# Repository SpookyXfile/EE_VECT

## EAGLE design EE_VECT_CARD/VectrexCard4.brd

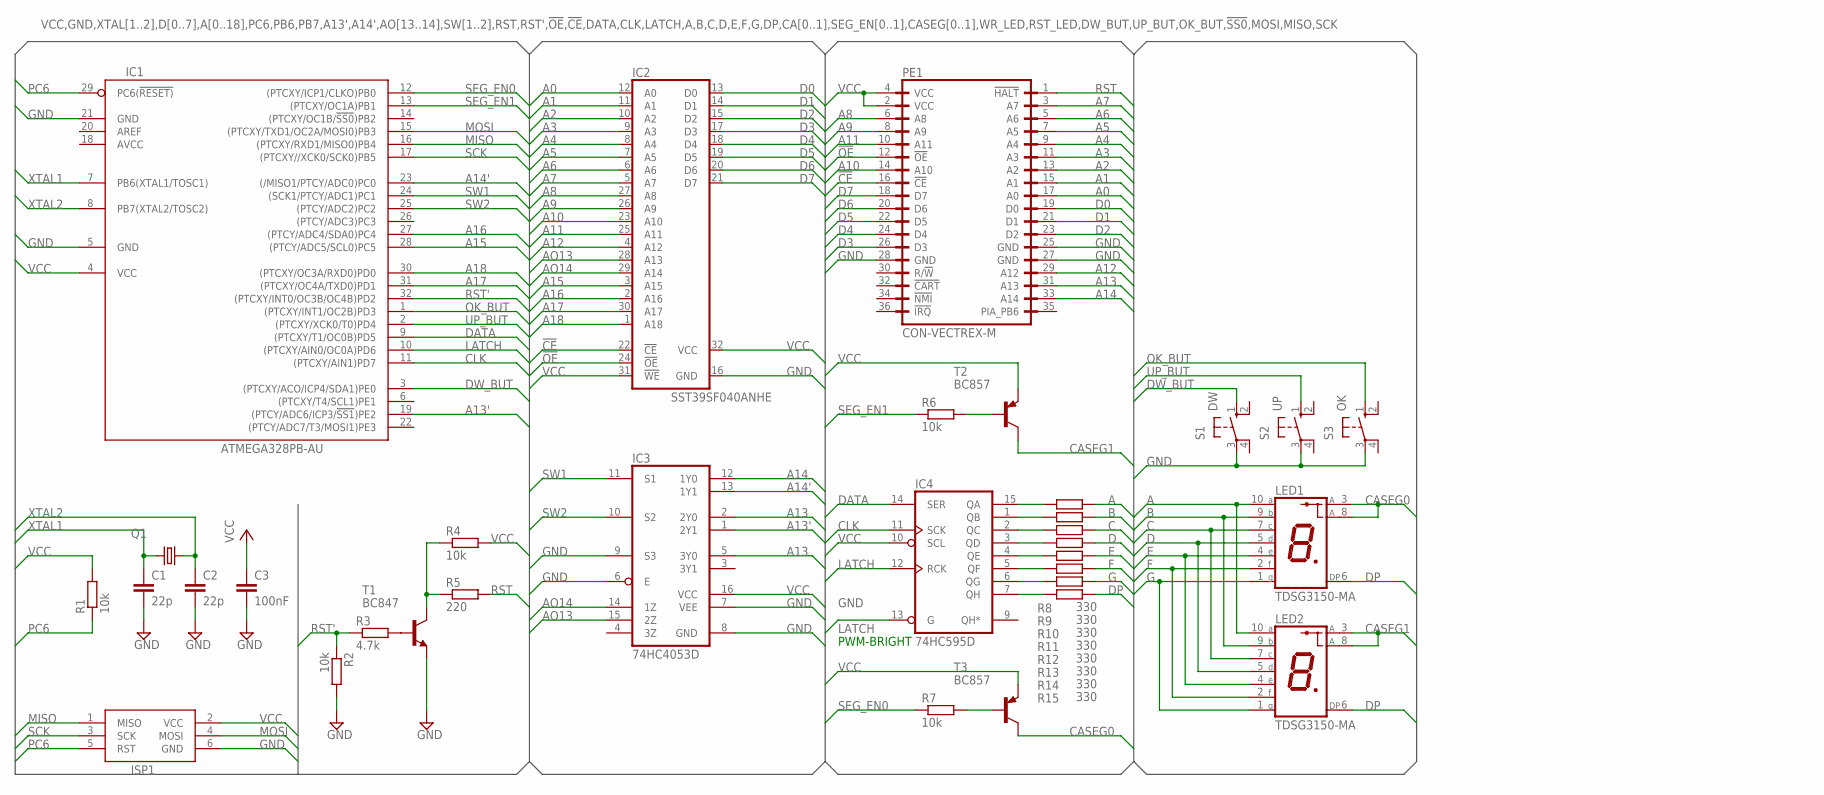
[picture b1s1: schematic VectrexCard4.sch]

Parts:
C1, C2: 22p; C2012
C3: 100nF; C050-025X075
IC1: ATMEGA328PB-AU; TQFP32-08
IC2: SST39SF040ANHE; S32
IC3: 74HC4053D; SO16
IC4: 74HC595D; SO16
ISP1: AVRISP-6; AVRISP
LED1, LED2: TDSG3150-MA; LA-401
PE1: CON-VECTREX-M; PCB_VECTREX_CONNECTOR
Q1: 8MHz; HC49U-V
R1: 10k; 0204/7
R2, R6, R7: 10k; M2012
R3: 4.7k; M2012
R4: 10k; R2012
R5: 220; R2012
R8, R9, R10, R11, R12, R13, R14, R15: 330; M2012
S1: DW; B3F-10XX
S2: UP; B3F-10XX
S3: OK; B3F-10XX
T1: BC847; SOT23
T2, T3: BC857; SOT23-BEC

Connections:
!CE: IC2.22 (!CE), PE1.16 (!CE)
!OE: IC2.24 (!OE), PE1.12 (!OE)
A: LED1.10 (A), LED2.10 (A), R8.2
A0: IC2.12 (A0), PE1.17 (A0)
A1: IC2.11 (A1), PE1.15 (A1)
A2: IC2.10 (A2), PE1.13 (A2)
A3: IC2.9 (A3), PE1.11 (A3)
A4: IC2.8 (A4), PE1.9 (A4)
A5: IC2.7 (A5), PE1.7 (A5)
A6: IC2.6 (A6), PE1.5 (A6)
A7: IC2.5 (A7), PE1.3 (A7)
A8: IC2.27 (A8), PE1.6 (A8)
A9: IC2.26 (A9), PE1.8 (A9)
A10: IC2.23 (A10), PE1.14 (A10)
A11: IC2.25 (A11), PE1.10 (A11)
A12: IC2.4 (A12), PE1.29 (A12)
A13: IC3.2 (2Y0), IC3.5 (3Y0), PE1.31 (A13)
A13': IC1.19 ((PTCY/ADC6/ICP3/!SS1!)PE2), IC3.1 (2Y1)
A14: IC3.12 (1Y0), PE1.33 (A14)
A14': IC1.23 ((/MISO1/PTCY/ADC0)PC0), IC3.13 (1Y1)
A15: IC1.28 ((PTCY/ADC5/SCL0)PC5), IC2.3 (A15)
A16: IC1.27 ((PTCY/ADC4/SDA0)PC4), IC2.2 (A16)
A17: IC1.31 ((PTCXY/OC4A/TXD0)PD1), IC2.30 (A17)
A18: IC1.30 ((PTCXY/OC3A/RXD0)PD0), IC2.1 (A18)
AO13: IC2.28 (A13), IC3.15 (2Z)
AO14: IC2.29 (A14), IC3.14 (1Z)
B: LED1.9 (B), LED2.9 (B), R9.2
C: LED1.7 (C), LED2.7 (C), R10.2
CASEG0: LED1.3 (A), LED1.8 (A), T3.C
CASEG1: LED2.3 (A), LED2.8 (A), T2.C
CLK: IC1.11 ((PTCXY/AIN1)PD7), IC4.11 (SCK)
D: LED1.5 (D), LED2.5 (D), R11.2
D0: IC2.13 (D0), PE1.19 (D0)
D1: IC2.14 (D1), PE1.21 (D1)
D2: IC2.15 (D2), PE1.23 (D2)
D3: IC2.17 (D3), PE1.26 (D3)
D4: IC2.18 (D4), PE1.24 (D4)
D5: IC2.19 (D5), PE1.22 (D5)
D6: IC2.20 (D6), PE1.20 (D6)
D7: IC2.21 (D7), PE1.18 (D7)
DATA: IC1.9 ((PTCXY/T1/OC0B)PD5), IC4.14 (SER)
DP: LED1.6 (DP), LED2.6 (DP), R15.2
DW_BUT: IC1.3 ((PTCXY/ACO/ICP4/SDA1)PE0), S1.1 (S)
E: LED1.4 (E), LED2.4 (E), R12.2
F: LED1.2 (F), LED2.2 (F), R13.2
G: LED1.1 (G), LED2.1 (G), R14.2
GND: C1.2, C2.2, C3.2, IC1.5 (GND), IC1.21 (GND), IC2.16 (GND), IC3.6 (E), IC3.7 (VEE), IC3.8 (GND), IC3.9 (S3), IC4.8 (GND), IC4.13 (G), ISP1.6 (GND), PE1.25 (GND), PE1.27 (GND), PE1.28 (GND), R2.2, S1.3, S2.3, S3.3, T1.2 (E)
LATCH: IC1.10 ((PTCXY/AIN0/OC0A)PD6), IC4.12 (RCK)
MISO: IC1.16 ((PTCXY/RXD1/MISO0)PB4), ISP1.1 (MISO)
MOSI: IC1.15 ((PTCXY/TXD1/OC2A/MOSI0)PB3), ISP1.4 (MOSI)
unnamed: IC4.7 (QH), R15.1
unnamed: IC4.15 (QA), R8.1
unnamed: IC4.1 (QB), R9.1
unnamed: IC4.2 (QC), R10.1
unnamed: IC4.3 (QD), R11.1
unnamed: IC4.4 (QE), R12.1
unnamed: IC4.5 (QF), R13.1
unnamed: IC4.6 (QG), R14.1
unnamed: R3.2, T1.1 (B)
unnamed: R6.2, T2.B
unnamed: R7.2, T3.B
unnamed: R4.1, R5.1, T1.3 (C)
OK_BUT: IC1.1 ((PTCXY/INT1/OC2B)PD3), S3.1 (S)
PC6: IC1.29 (PC6(!RESET)), ISP1.5 (RST), R1.1
RST: PE1.1 (!HALT), R5.2
RST': IC1.32 ((PTCXY/INT0/OC3B/OC4B)PD2), R2.1, R3.1
SCK: IC1.17 ((PTCXY//XCK0/SCK0)PB5), ISP1.3 (SCK)
SEG_EN0: IC1.12 ((PTCXY/ICP1/CLKO)PB0), R7.1
SEG_EN1: IC1.13 ((PTCXY/OC1A)PB1), R6.1
SW1: IC1.24 ((SCK1/PTCY/ADC1)PC1), IC3.11 (S1)
SW2: IC1.25 ((PTCY/ADC2)PC2), IC3.10 (S2)
UP_BUT: IC1.2 ((PTCXY/XCK0/T0)PD4), S2.1 (S)
VCC: C3.1, IC1.4 (VCC), IC2.31 (!WE), IC2.32 (VCC), IC3.16 (VCC), IC4.10 (SCL), IC4.16 (VCC), ISP1.2 (VCC), PE1.2 (VCC), PE1.4 (VCC), R1.2, R4.2, T2.E, T3.E
XTAL1: C1.1, IC1.7 (PB6(XTAL1/TOSC1)), Q1.2
XTAL2: C2.1, IC1.8 (PB7(XTAL2/TOSC2)), Q1.1

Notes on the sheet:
PWM-BRIGHT

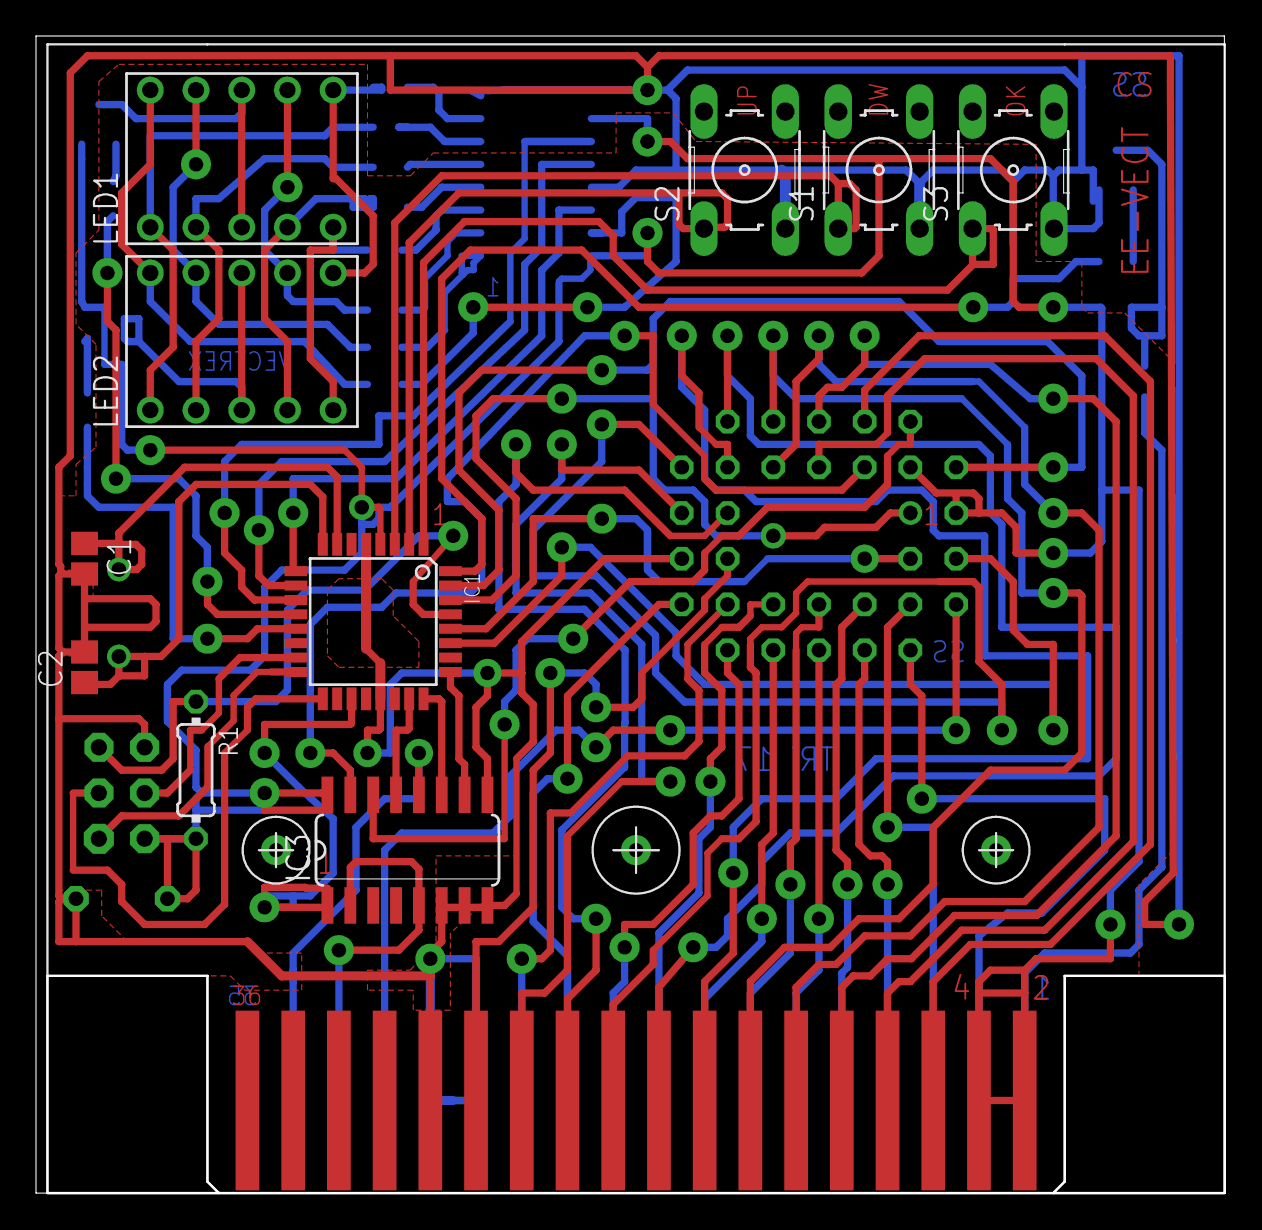
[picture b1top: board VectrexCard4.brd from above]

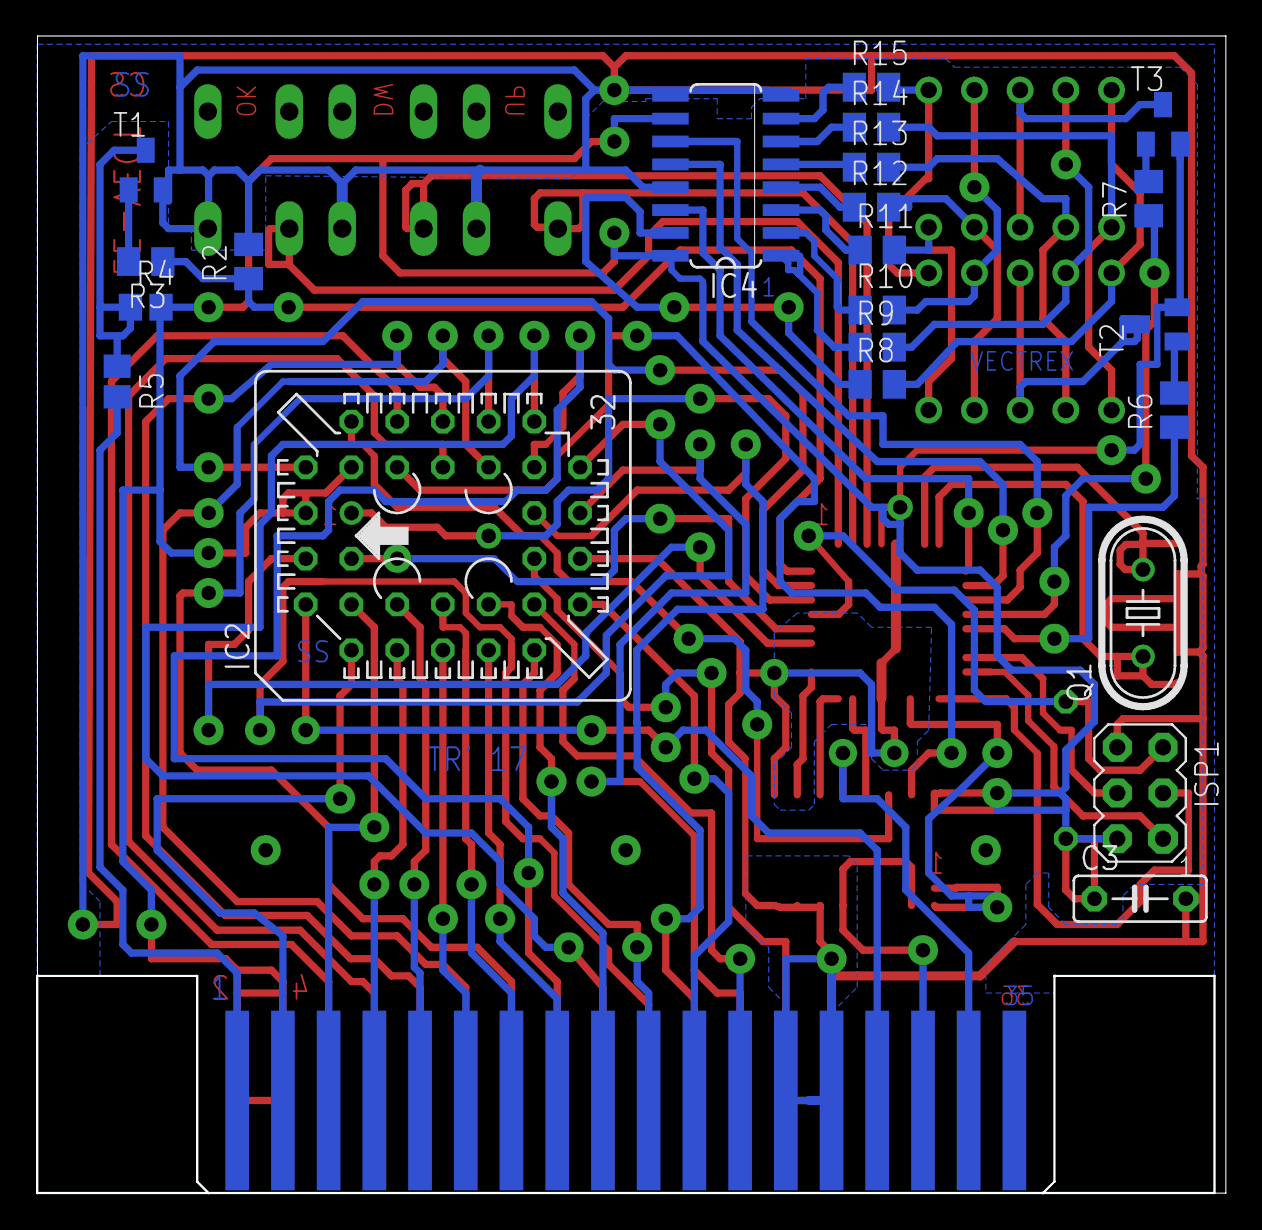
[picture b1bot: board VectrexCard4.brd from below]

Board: 3 copper layers, 66.0 x 64.2 mm, 33 parts (22 on the bottom side), 75 nets.

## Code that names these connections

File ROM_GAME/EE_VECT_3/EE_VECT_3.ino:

#include <EEPROM.h>


//	Atmega328PB Arduino Pin Translation 
#define DW_BUT_PIN    23
#define UP_BUT_PIN    4   // ( 4 )
#define OK_BUT_PIN    3   // ( 3 )

#define SDATA_PIN     5
#define LATCH_PIN     6
#define CLOCK_PIN     7
#define SEG_EN0_PIN   8   // ( PB0 )
#define SEG_EN1_PIN   9   // ( PB1 )


#define SW_ADDR_1_PIN		PIN_PC1   // ( 15 )
#define SW_ADDR_2_PIN		PIN_PC2   // ( 16 )
//#define SW_ADDR_A12_PIN		PIN_P**   //
#define SW_ADDR_A13_PIN		PIN_PE2   // ( 22 )
#define SW_ADDR_A14_PIN		PIN_PC0   // ( 14 )

#define ADDR_A15_PIN  		PIN_PC5   // 19
#define ADDR_A16_PIN  		PIN_PC4   // 18
#define ADDR_A17_PIN  		PIN_PD1
#define ADDR_A18_PIN  		PIN_PD0

#define RST_PIN		2


//  Set the EEPROM Addresses
//  |-------------------------------------------------------------------|
//  |	D7    	D6    	D5    	D4    	D3    	D2    	D1    	D0    	|
//  |-------------------------------------------------------------------|
//  |	A18     A17     A16     A15     AO14    AO13    SW1     SW2		|
//  |-------------------------------------------------------------------|
//static const uint8_t Addressing[] PROGMEM = { 0x03, 0x07, 0x0B, 0x0F, 0x13, 0x17, 0x1B, 0x1F, 0x23, 0x27, 0x2B, 0x2F, 0x33, 0x37, 0x3F, 0x47 };

static const uint8_t segNum[11]		PROGMEM = { 0xC0, 0xF9, 0xA4, 0xB0, 0x99, 0x92, 0x82, 0xF8, 0x80, 0x90, 0xBF };



uint8_t digit_1;
uint8_t digit_2;

uint8_t num;

uint8_t countByteBanks;

bool OK_seq;

bool toggle7SegLED;


uint8_t Addressing[63];

///////////////////////
// Helper Function  //
/////////////////////
void setPinHIGH( byte pin )
{
  digitalWrite( pin, HIGH );
}

void setPinLOW( byte pin )
{
  digitalWrite( pin, LOW );
}

void shiftOut( uint8_t dataPin, uint8_t latchPin, uint8_t clockPin, uint8_t val )
{
  uint8_t i;
  
  setPinLOW( LATCH_PIN );
  for ( i = 0; i < 8; ++i )
  {
    setPinLOW( CLOCK_PIN );
    //delayMicros( 50 );
      
    if ( !!( val & ( 1 << (7 - i) ) ) )
    {
      setPinHIGH( SDATA_PIN );
      //delayMicros( 50 );
    }
    else
    {
      setPinLOW( SDATA_PIN );
      //delayMicros( 50 );
    }
    
    setPinHIGH( CLOCK_PIN );
    //delayMicros( 50 );
  }
  setPinHIGH( LATCH_PIN );
  
}


//  Set the EEPROM Addresses
//  |-------------------------------------------------------------------|
//  |	D7    	D6    	D5    	D4    	D3    	D2    	D1    	D0    	|
//  |-------------------------------------------------------------------|
//  |	A18     A17     A16     A15     AO14    AO13    SW1     SW2		|
//  |-------------------------------------------------------------------|
void IO_Address( uint8_t setAddress )
{
  bool extractOctet = false;
  
  for ( uint8_t i=8; i > 0; --i )
  {
    extractOctet = (bool)( ( setAddress >> (i-1) ) & 0x01 );
    
    switch ( i-1 )
    {
      case 0 :
        //setPort( PORTC, SW_ADDR_1_PIN, extractOctet );
        ( extractOctet ) ? setPinHIGH( SW_ADDR_1_PIN ) : setPinLOW( SW_ADDR_1_PIN );
        break;
        
      case 1 :
        //setPort( PORTC, SW_ADDR_2_PIN, extractOctet );
        ( extractOctet ) ? setPinHIGH( SW_ADDR_2_PIN ) : setPinLOW( SW_ADDR_2_PIN );
        break;
      
      case 2 :
        //setPort( PORTE, SW_ADDR_A13_PIN, extractOctet );
        ( extractOctet ) ? setPinHIGH( SW_ADDR_A13_PIN ) : setPinLOW( SW_ADDR_A13_PIN );
        break;
      
      case 3 :
        //setPort( PORTC, SW_ADDR_A14_PIN, extractOctet );
        ( extractOctet ) ? setPinHIGH( SW_ADDR_A14_PIN ) : setPinLOW( SW_ADDR_A14_PIN );
        break;
      
      case 4 :
        //setPort( PORTC, ADDR_A15_PIN, extractOctet );
        ( extractOctet ) ? setPinHIGH( ADDR_A15_PIN ) : setPinLOW( ADDR_A15_PIN );
        break;
      
      case 5 :
        //setPort( PORTC, ADDR_A16_PIN, extractOctet );
        ( extractOctet ) ? setPinHIGH( ADDR_A16_PIN ) : setPinLOW( ADDR_A16_PIN );
        break;
      
      case 6 :
        //setPort( PORTD, ADDR_A17_PIN, extractOctet );
        ( extractOctet ) ? setPinHIGH( ADDR_A17_PIN ) : setPinLOW( ADDR_A17_PIN );
        break;
      
      case 7 :
        //setPort( PORTD, ADDR_A18_PIN, extractOctet );
        ( extractOctet ) ? setPinHIGH( ADDR_A18_PIN ) : setPinLOW( ADDR_A18_PIN );
        break;

      //default :
      //
      //  break;
    }
  }
}

void IO_Init( void )
{
  // define as output
  pinMode( SW_ADDR_1_PIN, OUTPUT );
  pinMode( SW_ADDR_2_PIN, OUTPUT );
  pinMode( SW_ADDR_A13_PIN, OUTPUT );
  pinMode( SW_ADDR_A14_PIN, OUTPUT );
  pinMode( ADDR_A15_PIN, OUTPUT );
  pinMode( ADDR_A16_PIN, OUTPUT );
  pinMode( ADDR_A17_PIN, OUTPUT );
  pinMode( ADDR_A18_PIN, OUTPUT );
  
  pinMode( SEG_EN0_PIN, OUTPUT );
  pinMode( SEG_EN1_PIN, OUTPUT );
  pinMode( SDATA_PIN, OUTPUT );
  pinMode( LATCH_PIN, OUTPUT );
  pinMode( CLOCK_PIN, OUTPUT );
  
  pinMode( RST_PIN, OUTPUT );
  

  // define as input & internal pullup
  pinMode( UP_BUT_PIN, INPUT_PULLUP );
  pinMode( OK_BUT_PIN, INPUT_PULLUP );
  pinMode( DW_BUT_PIN, INPUT_PULLUP );

  // define init 7 segment state
  setPinLOW( SDATA_PIN );
  setPinLOW( LATCH_PIN );
  setPinLOW( CLOCK_PIN );

  // define init reset state
  setPinHIGH( RST_PIN );

}


volatile bool awakeIntTimer = false;

volatile unsigned char  tickCount = 0;
volatile bool     awakeButton = false;

void InitTimer1()
{
  cli();
  
  TCCR1A = 0;
  TCCR1B = 0; 
  
  OCR1A = 0x138;    // 10ms Tick
  
  TCCR1B = ( 1 << WGM12 ) | ( 1 << CS12 );
  TIMSK1 = ( 1 << OCIE1A ); 
  
  sei(); 
  
}

// timer1 overflow interrupt
ISR ( TIMER1_COMPA_vect )
{
  ++tickCount;
  
  if ( tickCount >=20 )    //  120ms
  {
    awakeButton = true;
    tickCount = 0;
  }
  else
    awakeButton = false; 

  awakeIntTimer = true;
  
}

void SevenSegment( uint8_t value, bool dp, bool segEnable_1, bool segEnable_2 )
{
  setPinHIGH( SEG_EN0_PIN );
  setPinHIGH( SEG_EN1_PIN );
  
  // shift out the bits:
  shiftOut( SDATA_PIN, LATCH_PIN, CLOCK_PIN, value &= ( dp ) ? 0x7F : 0xFF );
  
  //delayMillis( 5 );
  
  if ( segEnable_1 )
    setPinLOW( SEG_EN0_PIN );
  else
    setPinHIGH( SEG_EN0_PIN );
  
  if ( segEnable_2 )
    setPinLOW( SEG_EN1_PIN );
  else
    setPinHIGH( SEG_EN1_PIN );
  
}

inline bool getButton_DW( void )
{
	
  return (bool)( digitalRead( DW_BUT_PIN ) );
}

inline bool getButton_UP( void )
{
  
  return (bool)( digitalRead( UP_BUT_PIN ) );
}

inline bool getButton_OK( void )
{
  
  return (bool)( digitalRead( OK_BUT_PIN ) );
}

volatile unsigned char DebounceSwitch( void )
{
  unsigned char Result = 0;
  
  cli();
  if ( awakeButton )
  {
    if ( !getButton_DW() == true )
    {
      Result = 2;
    }
        
    if ( !getButton_UP() == true )
    {
      Result = 4;
    }
    
    if ( !getButton_OK() == true )
    {
      Result = 8;
    }
  }
  else
  {
    Result = 0;
  }
  
  awakeButton = false;
  
  sei();
  
  return Result;
}

// -- SETUP -- //
void setup()
{     
	num = EEPROM.read( 0x02 );
	
	countByteBanks = EEPROM.read( 0x03 );
	
	for ( byte count = 0; count < countByteBanks;  count++ )
	{
		Addressing[count] = EEPROM.read( 0x10 + count );
	}
  
	if ( num < 1 || num > 60 )
		num = 1;
	
	IO_Init();
	//IO_Address( pgm_read_byte( &Addressing[num-1] ) );
	IO_Address( Addressing[num-1] );
      
	awakeIntTimer = false;
	InitTimer1();
    
	uint8_t digit_1 = 1;
	uint8_t digit_2 = 0;
  
	toggle7SegLED = true;
  
	OK_seq = false;
  
	//  Enable global interrupts
	sei();

}

void loop()
{
  if ( awakeIntTimer )
    {		
		//event to be executed every 12ms here
		volatile byte ButtonStatus = DebounceSwitch();
		
		
      //if ( !getButton_OK() )
      if ( ButtonStatus == 8 )
      {
        digit_1 = 10;
        digit_2 = 10;
        OK_seq = true;
      }
      else
      {
        //if ( !getButton_DW() )
        if ( ButtonStatus == 2 )
          num--;
        
        //if ( !getButton_UP() )
        if ( ButtonStatus == 4 )
          num++;
              
        digit_1 = num % 10;
        digit_2 = (uint8_t)( ( num / 10 ) % 10 );
      
        if ( (num < 1) || (num > 20) )
          num = 20;
      }
      
      if ( toggle7SegLED )
        SevenSegment( pgm_read_byte( &segNum[digit_2] ), false, false, true );
      else
        SevenSegment( pgm_read_byte( &segNum[digit_1] ), false, true, false );
                    
      toggle7SegLED ^= 1;
      
      if ( OK_seq )
      {
        delay( 500 );
        
        EEPROM.update( 0x02, num );
        
        //IO_Address( pgm_read_byte( &Addressing[num-1] ) );
		IO_Address( Addressing[num-1] );
        
        delay( 50 );
        
        setPinLOW( RST_PIN );
        delay( 330 );
        setPinHIGH( RST_PIN );
        
        OK_seq = false;
      }
	  
	  ButtonStatus = 0;
	  
	  awakeIntTimer = false;
    }

}
